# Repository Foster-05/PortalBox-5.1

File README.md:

# Portal Box 5.1.1
## A project by Bucknellians for Bucknellians, since 2013

*The currently implemented Portalbox, v2, in the Maker-E connected to a Prusa XL (left) and a v5.0.6 prototype (right).*

## Background
The Portalbox is an open-source makerspace management project. It originated at Bucknell University, in our makerspace the "Maker-E", and intends to spread worldwide, allowing makerspaces to control their equipment and their users as they see fit. The Portalbox focuses on using interlocks to control power to equipment, such as 3D printers or laser cutters, based on the RFID cards that each student possesses. I had the opportunity to work on v5 of the Portalbox over the summer of 2025, continuing into the academic year 25-26.

The Portalbox has been an ongoing project for roughly a decade, remaining open-source and created by students throughout its lifetime. Professor Joe Hass and software engineer TKEgan on GitHub have historically maintained the project for both firmware and backend development, including but not limited to the database and website access that's used by student techs to change permissions to each Portalbox. Find more information about the backend at [their Github](https://github.com/Bucknell-ECE/PortalBox-ManagementPortal).

<details>

<summary> Previous Implementation </summary>

## Current Implementation

As it stands, the Portalbox is in the MakerE and for the most part, working as intended. It includes a very simple I/O: A slot for an RFID card, a simple pushbutton, and on the back two power ports and a reset button. It utilizes a finite state machine design to work with RFID reader and button input to ascern what mode of functionality it should be in. As much of this functionality has been retained for the next iteration. 

Use of the current Portalbox is very simple, intentionally so. Simply place your RFID card, programmed by a technician or makerspace administrator, into the card slot. The Portalbox will light blue if you are marked as certified in an SQL database, and red if you're not. If it determines that you are certified, it will activate the power interlock and allow wall power to flow to the machine that it's connected to, be it a 3D printer, laser cutter, or soldering iron. When you remove your card, the box will begin blinking yellow and beeping at you. Pressing the button on the front will exit this "grace mode". Putting your card back in will accomplish the same as putting your card in originally. However, if you place in a card programmed as a "proxy card", the box will light orange and remain on. The result is that you may use the machine or leave it running, but keep your assigned RFID card with you. Finally, if a user assigned as a trainer in the database takes their card out of the box, a non-certified user may place theirs as a replacement. The box will light purple for "training" mode, allowing the user to temporarily keep the equipment active while learning how to use it. After they have been trained on the piece of equipment a technician can certify them so they may use it in the future.

Moving into developing a Version 5, we maintained several goals in mind: shrinking the footprint, increasing speed and reliability, and maintaining or improving functionality. The physical box is significantly smaller than its predecessor, reducing by an overall 11 square centimeters. Our improved platform has yet to be tested firmware-wise, but we hope the new microcontroller will significantly improve response times and state detection accuracy. Our modular approach to design and implementation has allowed for increased functionality and the previous design with a slot and button is still available if users so wish.
</details>

<details open>
<summary>Technical information</summary>

## Technical

*Portalbox v5.1.0 layout (left) and schematic (right)*

<details>
<summary>Power Interlock</summary>

### Overview
The Portalbox itself is powered off of 120Vrms from the wall, allowing for simpler placement and no worries or frustrations regarding battery power, lifetime, and so on. We use a hefty AC/DC converted to provide 5v power to the rest of the Portalbox, including the ESP32. We use relays to interlock wall power in between our two ports, one IEC C13 and one IEC C14. The female C13 is intended to be connected to wall power, while the male C14 is 15A fused output to makerspace equipment. We also include a current measurement IC to monitor power draw from a machine and monitor relay accuracy. Ensure that only 2 ounce copper is used when manufacturing: trace widths have been calculated to 2oz and traces may turn into fuses if incorrectly manufactured.
### Relay
We chose a [CUI Devices 20A relay](https://www.digikey.com/en/products/detail/same-sky-formerly-cui-devices/PR28-5V-360-1A-E/22522201?s=N4IgTCBcDa5mBmAtABwE5gBxIKwDckEA2ABiQEYBDJAUyQDsATEAXQF8g "Digikey") to ensure that our fuse would disconnect the circuit before any parts become damaged. The relay accepts the hot line from the wall and outputs it to the current measurement IC when the relay is activated. Activation is done using a simple [NMOS transistor](https://www.digikey.com/en/products/detail/diodes-incorporated/2N7002K-7/1934378?s=N4IgTCBcDa4HIHYAMSwGkC0CAiBJAwgCoZzYgC6AvkA "Digikey") circuit to allow for a 3v GPIO pin from the ESP32 to activate the relay using 5v (its required activation voltage). This specific transistor was chosen for availability, being pre-stocked in our space.

### Current Measurement
We're measuring current flowing from the wall out to the C14 port for a multitude of reasons. With proper implementation, this would allow for a measurement of "normal" current draw for any given machine, thus allowing continuous monitoring and flagging of any unusual or concerning behavior remotely. It would also allow us to retrieve records or throw a flag if our maximum of 15A is reached, thus requiring us to replace the onboard fuse. This would require some implementation with the existing MariaDB SQL database to store said current data and/or flags. Measurement is accomplished using an [Infineon IC](https://www.digikey.com/en/products/detail/infineon-technologies/TLE4971A050T5UE0001XUMA1/18700354?s=N4IgTCBcDaICoBkCiAWAnAdgIwFoCCADAKwFxE4CqOSBtWIAugL5A "Digikey") for this specific purpose. It's capable of +-120A, being much more than we need. It ouputs a variable voltage that depends on the current flowing through two major pads, allowing for later conversion into what specific current is being measured.
</details>

<details>
<summary>USB Interlock</summary>

### Overview
The Portalbox is equipped to provide data interlock through USB 2.0 between a USB-A port and a USB-C port. This is for specific applications such as the Maker-E's laser cutter, where proprietary power supply makes power interlock difficult. However, one is able to connect USB cables in between the cutter and a dedicated device to restrict data transfer of files required for laser cutting. It uses a similar relay structure to the power interlock to allow for robust switching.

### Relay
We use a [Standex-Meder](https://www.digikey.com/en/products/detail/standex-meder-electronics/DIP05-2A72-21L/2765346?s=N4IgTCBcDaICIEkAKAGArAWjAQQOxiwEYAZEAXQF8g "Digikey") DIP relay to allow for switching of data lines. It allows for simultaneous switching of two signals, which was necessary to interlock the D+/D- lines found in the USB 2.0 protocol. This particular relay may be out of stock and a Littelfuse equivealent is available. It's shown as excluded from the board in the schematic because we use a different [DIP header](https://www.digikey.com/en/products/detail/assmann-wsw-components/A-14-LC-TT/821743?s=N4IgTCBcDaIIIAICMAWAtAGQMJoCq5AF0BfIA "Digikey") J3 to allow for active switching of relays. Modularity is a big focus of the Portalbox, so switching of any components is ideal when possible.

### USB port design
We use typical four-pin USB-A 2.0 ports as well as USB-C ports capable of 3.0 on the board files seen above. They follow best practices found in the datasheet for design, including but not limited to ESD protection with diode system ICs U1 and U2. Both ports are always powered with 5v and have no data connection unless the above relays are active.
</details>

<details>
<summary>Peripherals and GPIO</summary>

While the power and data interlocks are the meat and potatoes of the Portalbox, our peripherals and GPIO is the seasoning. These focus on all of our miscellaneous functions, both new and old. Historically the boxes have been as simple to use as possible, including simply a card slot, single pushbutton, and RGB LEDs for feedback. This functionality has been retained, but we hope to significantly improve it for future use.

### Casing

Size has been another important factor of consideration while moving through the current version of the Portalbox. Initial versions were vertically stacked components, so they were relatively compact and fit in the space well. The versions currently implemented moved away from the vertical architecture, so they expanded significantly in footprint next to machinery in the Maker-E. Beginning our project, we wanted to ensure that we could shrink this footprint at least a little bit so the Portalbox would be more usable and widely applicable for most makerspaces. Above is pictured a version 5.0.6 (left), which is the same size as a version 5.1, next to a currently implemented Portalbox (right). The difference is apparent.

#### Materials and Design

Previously Portalboxes were all made out of lasercut acrylic, which was intentionally a semi-transparent material designed to be opaque but let LED light through to color the box itself. This design has worked very well, but we had serveral quarrels with it when starting the project. First and foremost, it was very painful to construct. The pieces had to fit together very precisely and use Very Heavy Bond tape to stick together long-term. The acrylic material was also expensive to acquire. We found that the original reasoning to choose acrylic was that makerspaces would be able to manufacture their own cases if they had a laser cutter on hand, as we did. Considering this design decision, we chose to move the Portalbox to a 3D printed enclosure. Nowadays, especially in the ECE space, 3D printers are a staple of iterative design and most makerspaces have access to at least one. We tested multiple filament types and determined that Jessie Transparent PLA was strong yet still let through the appropriate amount of light from LEDs mounted on the board. Gyroid infill patterns also provide fun effects! While designing the case, we were focused on ensuring modularity and ease of use. The case is designed to snap together using dovetails and require no adhesive or tape to stay together long-term. Said dovetails also provide interesting opportunities for modularity.

#### Modularity

Utilizing the 3D printed nature of the case and the dovetail design, we determined a method to standardize our design and allow for some of the open-source mindset to enhance the Portalbox. First and foremost, the Portalbox case was designed with options in mind. There are multiple inputs and outputs that one can choose to use with the Portalbox and that will work natively and immediately with the firmware, all of which have case pieces designed to fit them. There are also options to fit the same inputs and outputs on different sides of the case for alternate mounting options. The peak of modularity can be seen on the top part of the case, where it simply features two large holes containing dovetails to slot other pieces into. With this design, we're able to manufacture modules which best fit our use-case: from touchscreens to buttons to card readers, it provides nearly unlimited opportunity to design what you want for your makerspace and customize your Portalbox appropriately. We hope that the nature of this design will encourage others to participate and begin designing alternate components that will work with all the previous ones we've provided as a starting point.

### User Feedback

Along with the above mention of modularity, we wanted to ensure that this version of the Portalbox would be able to continue in its current function as well as extend to new applications. Therefore, we kept all of the same standard inputs and outputs: a piezo buzzer to alert users, RGB addressable LEDs to provide status of the box, a simple button for a multifunctional input, and an RFID reader for the typical "slot" application. We also extended some of the more technical user feedback by including test points for important nets, as well as mono-color feedback LEDs for 5v power, AC relay activation, and USB relay activation. A reset button broken out to the user is also available in the case of a manual reset becoming necessary. However, with the aforementioned modular case, we also included some other options for administrators. The firmware provides for a "tap" mode, where users no longer have to leave their card inside a Portalbox to use equipment. They can simply tap it on the case, and a "proxy" mode will be handled all in software instead of requiring physical proxy cards. We also added a ribbon cable connector for Adafruit's Eye-SPI technology, making interfacing with one of their [ILI9341 capacitative touch displays](https://www.adafruit.com/product/2090 "Adafruit") simple to implement. We hope that this will spruce up our space and make the Portalboxes even easier to use, while not precluding previous use-cases.
</details>

<details>
<summary>Microcontroller</summary>

### History

Historically, the Portalbox has been through every microcontroller you can think of. An original iteration used RP2040 breakout boards to do all processing on the platform, and connected a Pi Zero W to it for WiFi and API calling capabilities. Some time after that, a Raspberry Pi 4 was used to accomplish both tasks on one platform - at this point the Portalbox was running a full Linux OS with some firmware stored on it that would run upon boot.

During our time with the project, one of our main goals was to move platform to something that was smaller, less expensive, and more apt for the task. We chose to use the ESP32 platform, as it would still give us full internet capabilities while in a smaller form factor and with plenty of processing power to do the job. This turned our major limitation into GPIO.

We deliberately chose to utilize a [full devkit from Espressif](https://www.digikey.com/en/products/detail/espressif-systems/ESP32-S3-DEVKITC-1-N8R8/15295894 "Digikey") instead of simply placing the chip on our board. This decision was made for a multitude of reasons, but chief among them was that it made our lives easier and will continue to be effective far into the future. Long story short, all of the onboard electronics already included allowed us to focus on development of our other systems instead of worrying about setting up JTAG and the like. It also allows us to simply replace an entire module if something fails in the future, meaning these boards will be able to be used far into the future by simply replacing components and preventing the trashing of an entire board due to an oversight or failure.

Accordingly, we chose the Espressif devkit because they provide the most complete hardware output, as well as a fleshed out ESP-IDF toolchain for natively flashing boards if necessary. Specifically, the Espressif ESP32-S3-Devkit-C1 breaks out nearly all of the onboard GPIO so we can fit in all of our components that we need to and leave several pins for further expansion if we so desire. We originally began development with the ESP32-C6 devkit, but found it was too limited for our needs. The S3, specifically the C1-N8R8 revision, takes a larger footprint of the board but has proportionately more GPIO. Also beware of off-brand or alternate suppliers of devkits, as we found some with the same functionality but a very different physical footprint, being longer and skinnier. Be aware of the difference and make sure to purchase from Digikey or Adafruit. 

At different points we utilized ESP-IDF to flash our devkits with a custom build of Micropython. All firmware for the Portalbox is currently written in Micropython. There's a big focus on connectivity, and getting access to WPA3-Enterprise networks was a goal of ours. These networks are extremely common at universities and would make spreading the Portalbox much easier if they will natively hook up to existing WiFi networks. This is currently not implemented, as Micropython does not natively support Enterprise networks. There's a pending pull request that would implement it, so hopefully soon this capability will be added. In the meantime, our boxes are connected to the hidden Personal-class network on campus used in our engineering building.
</details>

<details>
<summary>Certification Compliance</summary>
The Portalbox has been designed to as closely as possible comply with IPC-2221 for General Design, and more specifically for IPC-2222 Rigid design specifications. Please make us aware of any discrepancies that may come up.
</details>

</details>

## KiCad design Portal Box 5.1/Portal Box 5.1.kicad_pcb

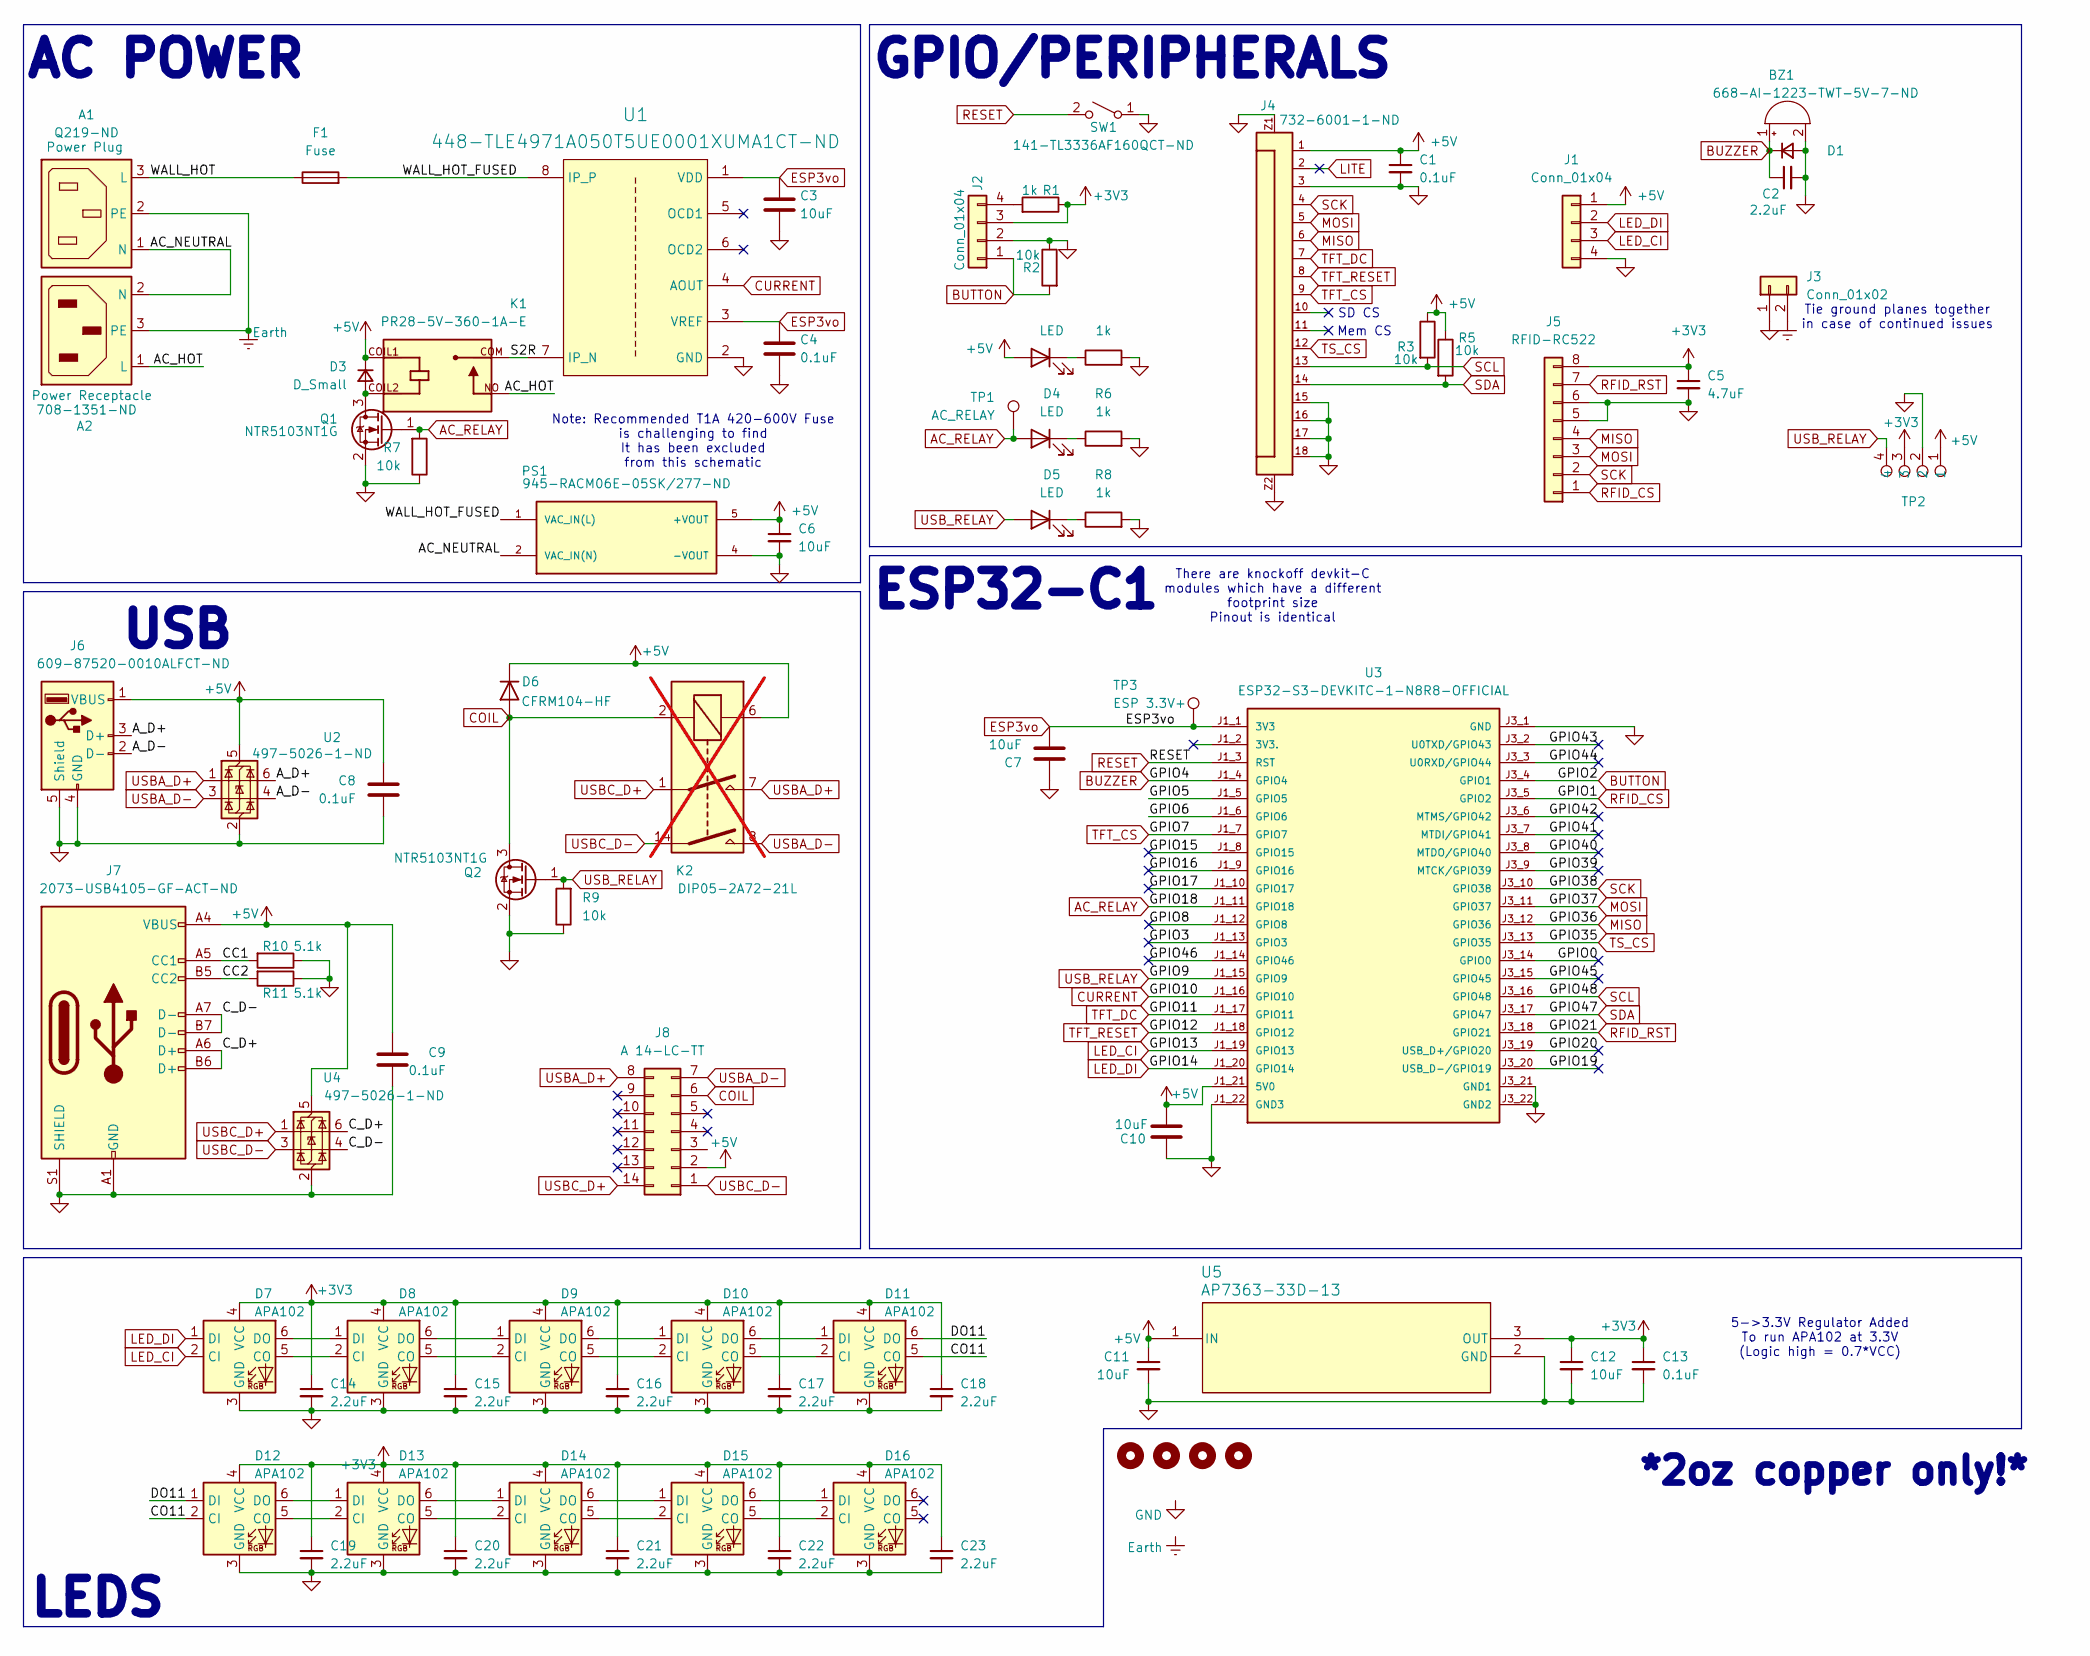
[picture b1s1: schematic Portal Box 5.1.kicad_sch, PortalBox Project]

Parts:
A1: Q219-ND; QUALTEK_703W-00_53; Part No Q219-ND
A2: 708-1351-ND; BULGIN_PX0675_PC
BZ1: 668-AI-1223-TWT-5V-7-ND; XDCR_AI-1223-TWT-3V-2-R
C1, C4, C8, C9, C13: 0.1uF; C_0805_2012Metric
C2, C14, C15, C16, C17, C18, C19, C20, C21, C22, C23: 2.2uF; C_0805_2012Metric
C3, C6, C7, C10, C11, C12: 10uF; C_0805_2012Metric
C5: 4.7uF; C_0805_2012Metric
D1, D3: D_Small; D_SOD-123
D2, D4, D5: LED; WL-SMTW_3528
D6: CFRM104-HF; D_SOD-123
D7, D8, D9, D10, D11, D12, D13, D14, D15, D16: APA102; LED_RGB_5050-6
F1: Fuse; Fuse_Custom
H1, H2, H3, H4: MountingHole; MountingHole_3.2mm_M3
J1, J2: Conn_01x04; PinHeader_1x04_P2.54mm_Vertical
J3: Conn_01x02; PinHeader_1x02_P2.54mm_Vertical
J4: 732-6001-1-ND; adafruit_ribbon_conn
J5: RFID-RC522; PinHeader_1x08_P2.54mm_Vertical
J6: 609-87520-0010ALFCT-ND; AMPHENOL_87520-0010ALF
J7: 2073-USB4105-GF-ACT-ND; GCT_USB4105-GF-A
J8: A 14-LC-TT; DIP-14_W7.62mm
K1: PR28-5V-360-1A-E; RELAY_PR28-5V-360-1A-E; PARTREV 1.01
K2: DIP05-2A72-21L; Relay_StandexMeder_DIP_LowProfile; not fitted
PS1: 945-RACM06E-05SK/277-ND; CONV_RACM06E-05SK_277; PARTREV PRELIMINARY
Q1, Q2: NTR5103NT1G; SOT-23
R1, R4, R6, R8: 1k; R_0805_2012Metric
R2, R3, R5, R7, R9: 10k; R_0805_2012Metric
R10, R11: 5.1k; R_0805_2012Metric
SW1: 141-TL3336AF160QCT-ND; SW_TL3336AF160Q
TP1: AC_RELAY; TestPoint_Pad_D1.5mm
TP2: FourTPs
TP3: ESP 3.3V+; TestPoint_Pad_D1.5mm
U1: 448-TLE4971A050T5UE0001XUMA1CT-ND; TLE4971
U2, U4: 497-5026-1-ND; SOT-666
U3: ESP32-S3-DEVKITC-1-N8R8-OFFICIAL
U5: AP7363-33D-13; TO-252-2

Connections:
+3V3: C5.1, C12.1, C13.1, C14.1, C15.1, C16.1, C17.1, C18.1, C19.1, C20.1, C21.1, C22.1, C23.1, D7.4 (VCC), D8.4 (VCC), D9.4 (VCC), D10.4 (VCC), D11.4 (VCC), D12.4 (VCC), D13.4 (VCC), D14.4 (VCC), D15.4 (VCC), D16.4 (VCC), J2.3, J5.8, R1.1, TP2.3, U5.3 (OUT)
+5V: C1.1, C6.1, C8.1, C9.1, C10.2, C11.1, D2.2 (A), D3.1 (K), D6.1 (K), J1.1, J4.1, J6.1 (VBUS), J7.A4 (VBUS), J7.A9 (VBUS), J7.B4 (VBUS), J7.B9 (VBUS), J8.2, K1.COIL1, K2.6, PS1.5 (+VOUT), R3.1, R5.1, TP2.1, U2.5 (VBUS), U3.J1_21 (5V0), U4.5 (VBUS), U5.1 (IN)
/AC_HOT: A2.1 (L), K1.NO
/AC_NEUTRAL: A1.1 (N), A2.2 (N), PS1.2 (VAC_IN(N))
/A_D+: J6.3 (D+), U2.6 (I/O1)
/A_D-: J6.2 (D-), U2.4 (I/O2)
/CC1: J7.A5 (CC1), R10.2
/CC2: J7.B5 (CC2), R11.2
/CO11: D11.5 (CO), D12.2 (CI)
/C_D+: J7.A6 (D+), J7.B6 (D+), U4.6 (I/O1)
/C_D-: J7.A7 (D-), J7.B7 (D-), U4.4 (I/O2)
/DO11: D11.6 (DO), D12.1 (DI)
/GPIO0: U3.J3_14 (GPIO0)
/GPIO3: U3.J1_13 (GPIO3)
/GPIO5: U3.J1_5 (GPIO5)
/GPIO6: U3.J1_6 (GPIO6)
/GPIO8: U3.J1_12 (GPIO8)
/GPIO15: U3.J1_8 (GPIO15)
/GPIO16: U3.J1_9 (GPIO16)
/GPIO17: U3.J1_10 (GPIO17)
/GPIO19: U3.J3_20 (USB_D-/GPIO19)
/GPIO20: U3.J3_19 (USB_D+/GPIO20)
/GPIO39: U3.J3_9 (MTCK/GPIO39)
/GPIO40: U3.J3_8 (MTDO/GPIO40)
/GPIO41: U3.J3_7 (MTDI/GPIO41)
/GPIO42: U3.J3_6 (MTMS/GPIO42)
/GPIO43: U3.J3_2 (U0TXD/GPIO43)
/GPIO44: U3.J3_3 (U0RXD/GPIO44)
/GPIO45: U3.J3_15 (GPIO45)
/GPIO46: U3.J1_14 (GPIO46)
/S2R: K1.COM, U1.7 (IP_N)
/WALL_HOT: A1.3 (L), F1.1
/WALL_HOT_FUSED: F1.2, PS1.1 (VAC_IN(L)), U1.8 (IP_P)
AC_RELAY: D4.2 (A), Q1.1 (G), R7.2, TP1.1, U3.J1_11 (GPIO18)
BUTTON: J2.1, R2.2, U3.J3_4 (GPIO1)
BUZZER: BZ1.1 (+), C2.1, D1.1 (K), U3.J1_4 (GPIO4)
COIL: D6.2 (A), J8.6, K2.2, Q2.3 (D)
CURRENT: U1.4 (AOUT), U3.J1_16 (GPIO10)
ESP3vo: C3.1, C4.1, C7.2, TP3.1, U1.1 (VDD), U1.3 (VREF), U3.J1_1 (3V3)
Earth: A1.2 (PE), A2.3 (PE), J3.2
GND: BZ1.2 (-), C1.2, C2.2, C3.2, C4.2, C5.2, C6.2, C7.1, C8.2, C9.2, C10.1, C11.2, C12.2, C13.2, C14.2, C15.2, C16.2, C17.2, C18.2, C19.2, C20.2, C21.2, C22.2, C23.2, D1.2 (A), D7.3 (GND), D8.3 (GND), D9.3 (GND), D10.3 (GND), D11.3 (GND), D12.3 (GND), D13.3 (GND), D14.3 (GND), D15.3 (GND), D16.3 (GND), J1.4, J2.2, J3.1, J4.3, J4.15, J4.16, J4.17, J4.18, J4.Z1, J4.Z2, J5.5, J5.6, J6.4 (GND), J6.5 (Shield), J7.A1 (GND), J7.A12 (GND), J7.B1 (GND), J7.B12 (GND), J7.S1 (SHIELD), PS1.4 (-VOUT), Q1.2 (S), Q2.2 (S), R2.1, R4.2, R6.2, R7.1, R8.2, R9.1, R10.1, R11.1, SW1.1 (A), TP2.2, U1.2 (GND), U2.2 (GND), U3.J1_22 (GND3), U3.J3_1 (GND), U3.J3_21 (GND1), U3.J3_22 (GND2), U4.2 (GND), U5.2 (GND)
LED_CI: D7.2 (CI), J1.3, U3.J1_19 (GPIO13)
LED_DI: D7.1 (DI), J1.2, U3.J1_20 (GPIO14)
LITE: J4.2
MISO: J4.6, J5.4, U3.J3_12 (GPIO36)
MOSI: J4.5, J5.3, U3.J3_11 (GPIO37)
unnamed: D2.1 (K), R4.1
unnamed: D3.2 (A), K1.COIL2, Q1.3 (D)
unnamed: D4.1 (K), R6.1
unnamed: D5.1 (K), R8.1
unnamed: D7.5 (CO), D8.2 (CI)
unnamed: D7.6 (DO), D8.1 (DI)
unnamed: D8.5 (CO), D9.2 (CI)
unnamed: D8.6 (DO), D9.1 (DI)
unnamed: D9.5 (CO), D10.2 (CI)
unnamed: D10.5 (CO), D11.2 (CI)
unnamed: D9.6 (DO), D10.1 (DI)
unnamed: D10.6 (DO), D11.1 (DI)
unnamed: D12.5 (CO), D13.2 (CI)
unnamed: D12.6 (DO), D13.1 (DI)
unnamed: D13.5 (CO), D14.2 (CI)
unnamed: D13.6 (DO), D14.1 (DI)
unnamed: D14.5 (CO), D15.2 (CI)
unnamed: D14.6 (DO), D15.1 (DI)
unnamed: D15.5 (CO), D16.2 (CI)
unnamed: D15.6 (DO), D16.1 (DI)
unnamed: J2.4, R1.2
RESET: SW1.2 (B), U3.J1_3 (RST)
RFID_CS: J5.1, U3.J3_5 (GPIO2)
RFID_RST: J5.7, U3.J3_18 (GPIO21)
SCK: J4.4, J5.2, U3.J3_10 (GPIO38)
SCL: J4.13, R3.2, U3.J3_16 (GPIO48)
SDA: J4.14, R5.2, U3.J3_17 (GPIO47)
TFT_CS: J4.9, U3.J1_7 (GPIO7)
TFT_DC: J4.7, U3.J1_17 (GPIO11)
TFT_RESET: J4.8, U3.J1_18 (GPIO12)
TS_CS: J4.12, U3.J3_13 (GPIO35)
USBA_D+: J8.8, K2.7, U2.1 (I/O1)
USBA_D-: J8.7, K2.8, U2.3 (I/O2)
USBC_D+: J8.14, K2.1, U4.1 (I/O1)
USBC_D-: J8.1, K2.14, U4.3 (I/O2)
USB_RELAY: D5.2 (A), Q2.1 (G), R9.2, TP2.4, U3.J1_15 (GPIO9)

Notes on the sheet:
Mem CS
5->3.3V Regulator Added To run APA102 at 3.3V (Logic high = 0.7*VCC)
Tie ground planes together in case of continued issues
AC POWER
ESP32-C1
SD CS
GPIO/PERIPHERALS
*2oz copper only!*
LEDS
Note: Recommended T1A 420-600V Fuse is challenging to find It has been excluded from this schematic
USB
There are knockoff devkit-C modules which have a different footprint size Pinout is identical

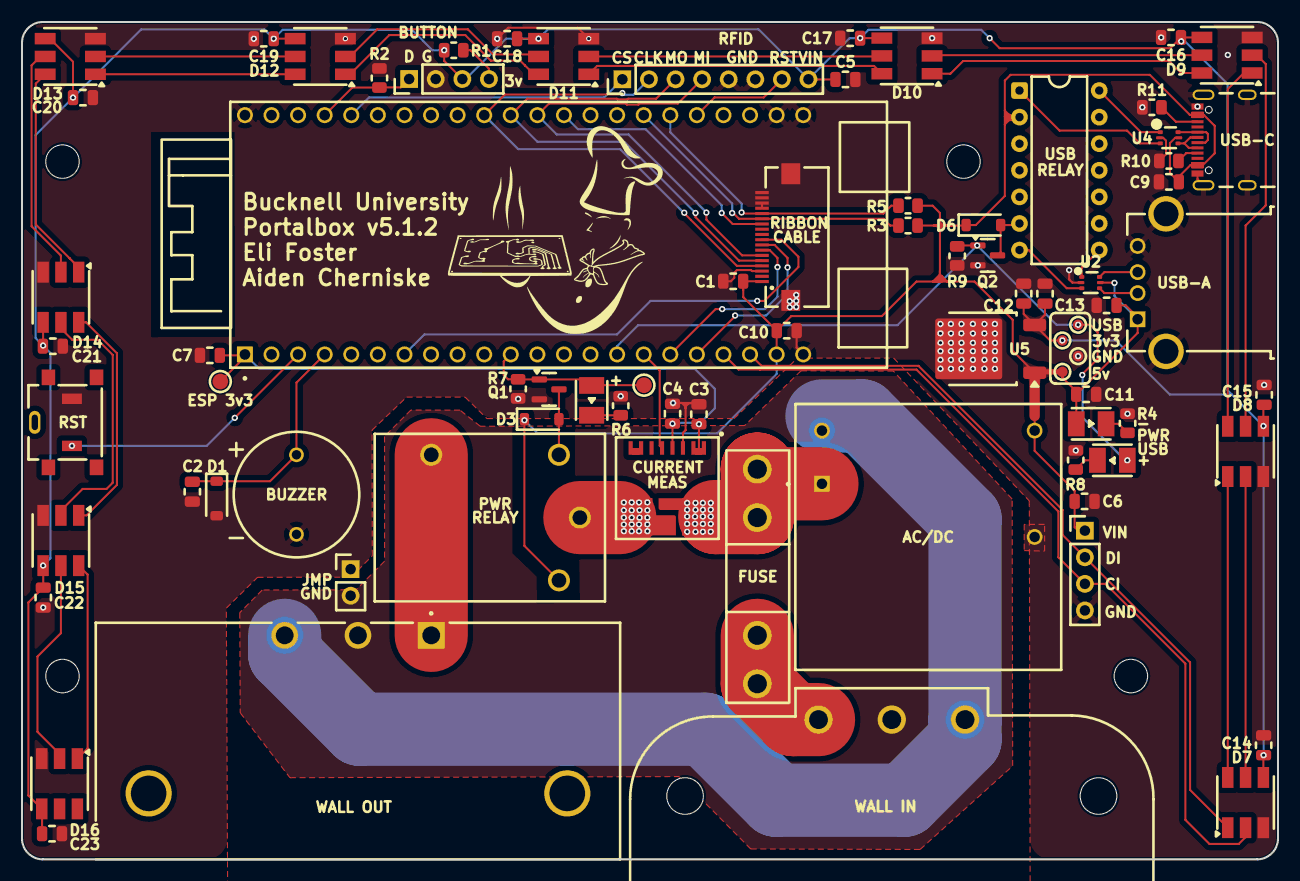
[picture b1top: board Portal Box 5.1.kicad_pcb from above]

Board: 2 copper layers, 120.0 x 80.0 mm, 79 parts (0 on the bottom side), 63 nets.

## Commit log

2025-10-25 add gitignore
2025-10-25 Add 5.1 Files
    Add 5.1.0 files from version pushed to production for testing.
2025-10-25 Add images
2025-10-26 add images, readme updated w/ shields, interlock sections
2025-10-27 add 2oz copper notification, update readme
2025-10-27 fix intro images
2025-10-27 fix intro images on separate rows
2025-10-27 fix rows again
2025-10-28 add mcu img, update readme
2025-10-28 update track clearances, mfg files
2025-10-28 changed some part numbers, update csv
2025-10-29 split images, update microcontroller section of readme
2025-10-29 complete microcontroller section of readme
2025-10-29 complete gpio section
2025-10-29 finish gpio section
2025-10-29 write previous implementation section
2025-10-29 fix previous implementation section
2025-10-29 fix previous caption
2025-11-03 update compliance section
2025-11-03 update current implementation
2026-02-12 change ac/dc and acm to dc ground, update planes
2026-02-26 push from laptop
2026-02-26 fix ground plane bulges, schematic and layout change for TVS diodes
2026-02-26 move r2 and fix silkscreening, update tvs diode footprint
2026-02-26 update revision number :)
2026-02-26 Update version from 5.1.0 to 5.1.1 in README
2026-03-03 schematic updates, added ground jumper
2026-03-05 update component labels
2026-03-16 chore: fix labels, solid pad connections, and version no.
2026-03-16 fix labels
2026-03-17 fix drc errors and remove tp4 reference
2026-03-19 Update README with Makerportal github link
